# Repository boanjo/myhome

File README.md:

# myhome
A collection of mysensors nodes, gateways and HW from my home

I use a mix of NRF (2.4GHz) and RFM69 (433MHz) depending on the usage of the sensor. For longer distances i use RFM69 but they are a bit more power hungry so they all fill a purpose

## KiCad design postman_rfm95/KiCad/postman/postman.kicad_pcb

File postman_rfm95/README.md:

# Weather Station DC powered
This is my weatherstation for long range communication (20-100m) based on the MySensors framework https://www.mysensors.org/

The weather station is connecting 3 different sensors with water protected connections and casing. I've used a Adafruit PermaProto 1/2 sized board which works well here since it's mainly soldering of connectors we need to do and a few resistors.

The focus for this model is to protect the GX12 connections and the PCB but this with easy access. The box has plenty of room for the homemade 433MHz antenna:  http://www.byvac.com/downloads/RLnn/How-to-make-a-Air-Cooled-433MHz-antenna.pdf.

Fusion 360 - 3D printed parts
Download model from: https://www.thingiverse.com/thing:4652239

Youtube video: https://youtu.be/E27CFRdZH9k

Enjoy!

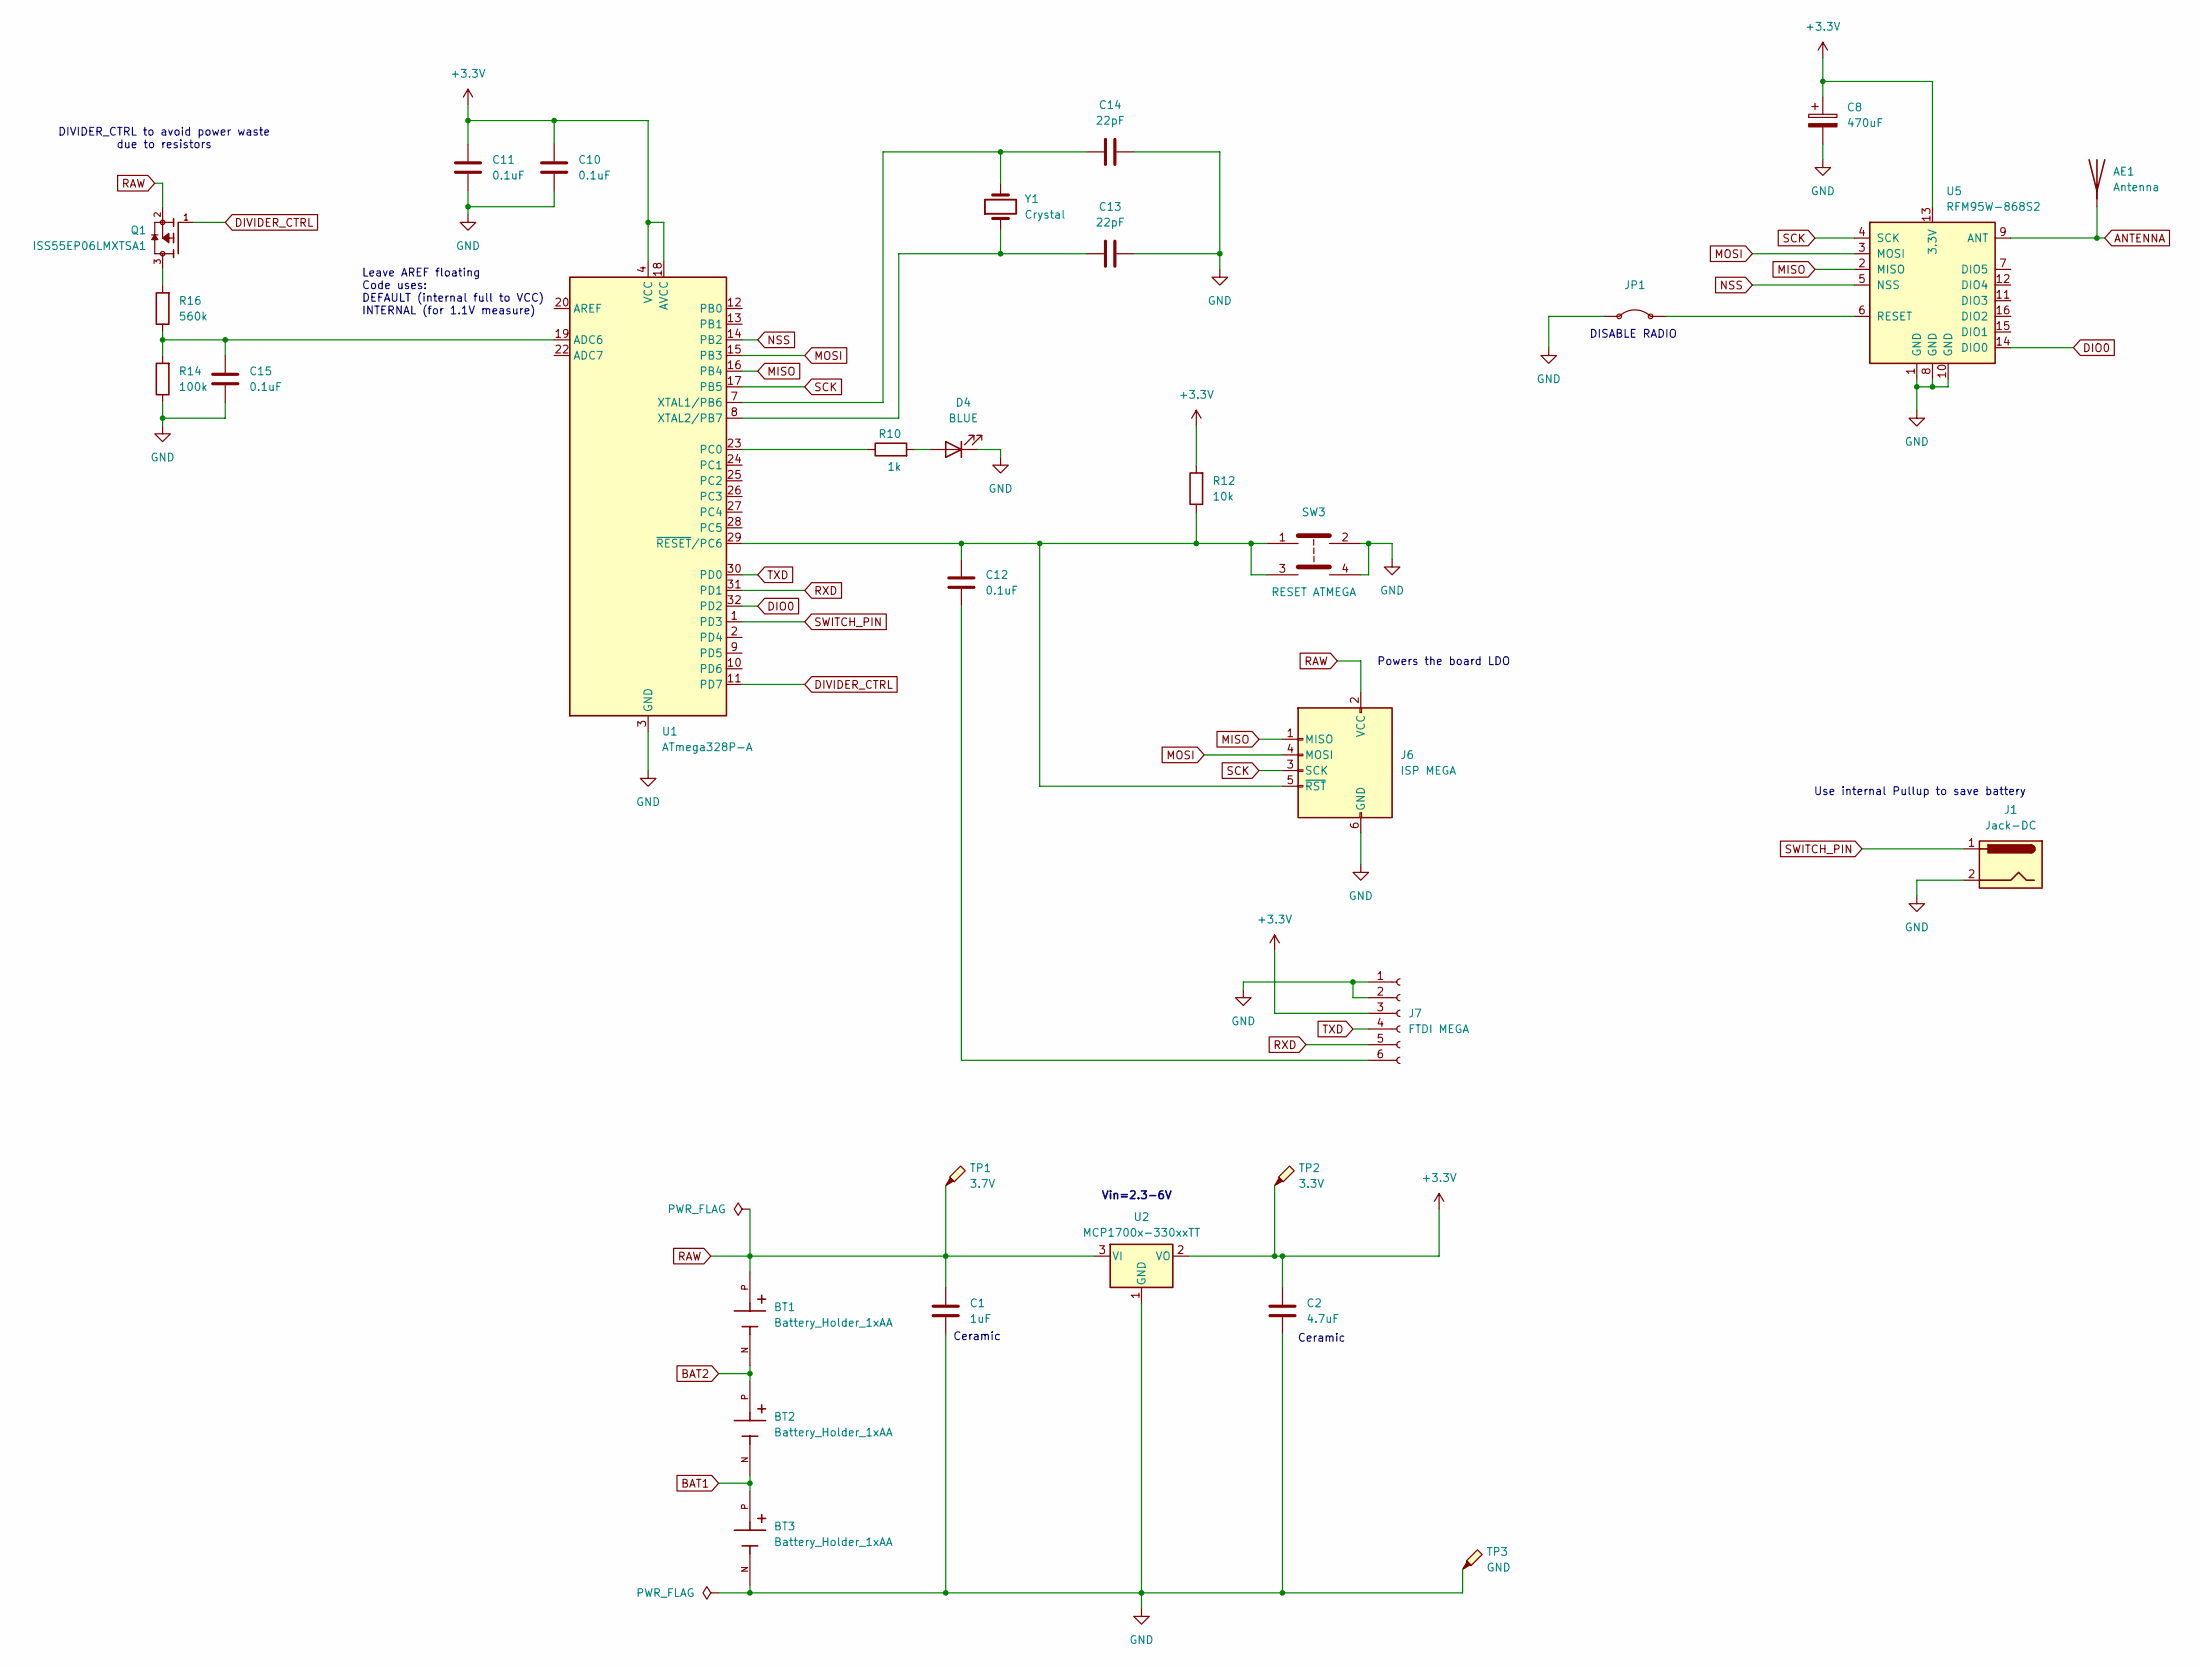
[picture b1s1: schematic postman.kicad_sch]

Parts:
AE1: Antenna; Antenna 868MHz
BT1, BT2, BT3: Battery_Holder_1xAA; Battery Holder 1xAA; PARTREV C
C1: 1uF; C_0805_2012Metric_Pad1.18x1.45mm_HandSolder
C2: 4.7uF; C_0805_2012Metric_Pad1.18x1.45mm_HandSolder
C8: 470uF; CP_Elec_10x10.5
C10, C11, C12, C15: 0.1uF; C_0805_2012Metric_Pad1.18x1.45mm_HandSolder
C13, C14: 22pF; C_0805_2012Metric_Pad1.18x1.45mm_HandSolder
D4: BLUE; LED_0805_2012Metric_Pad1.15x1.40mm_HandSolder
J1: Jack-DC; Jack DC
J6: ISP MEGA; AVR ISP 6p
J7: FTDI MEGA; FTDI 6p
JP1: Jumper 2p
Q1: ISS55EP06LMXTSA1; SOT-23_Handsoldering
R10: 1k; R_0805_2012Metric_Pad1.20x1.40mm_HandSolder
R12: 10k; R_0805_2012Metric_Pad1.20x1.40mm_HandSolder
R14: 100k; R_0805_2012Metric_Pad1.20x1.40mm_HandSolder
R16: 560k; R_0805_2012Metric_Pad1.20x1.40mm_HandSolder
SW3: RESET ATMEGA; tactile smd 13019319
TP1: 3.7V; Pin_D1.0mm_L10.0mm
TP2: 3.3V; Pin_D1.0mm_L10.0mm
TP3: GND; Pin_D1.0mm_L10.0mm
U1: ATmega328P-A; TQFP-32_7x7mm_P0.8mm
U2: MCP1700x-330xxTT; SOT-23_Handsoldering
U5: RFM95W-868S2; HOPERF_RFM9XW_SMD
Y1: Crystal; Crystal SMD FOXSDLF08020

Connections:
+3.3V: C2.1, C8.1, C10.1, C11.1, J7.3, R12.2, TP2.1, U1.4 (VCC), U1.6 (VCC), U1.18 (AVCC), U2.2 (VO), U5.13 (3.3V)
ANTENNA: AE1.1 (A), U5.9 (ANT)
BAT1: BT2.N, BT3.P
BAT2: BT1.N, BT2.P
DIO0: U1.32 (PD2), U5.14 (DIO0)
DIVIDER_CTRL: Q1.1, U1.11 (PD7)
GND: BT3.N, C1.2, C2.2, C8.2, C10.2, C11.2, C13.2, C14.2, C15.2, D4.1 (K), J1.2, J6.6 (GND), J7.1, J7.2, JP1.1, R14.1, SW3.2, SW3.4, TP3.1, U1.3 (GND), U1.5 (GND), U1.21 (GND), U2.1 (GND), U5.1 (GND), U5.8 (GND), U5.10 (GND)
MISO: J6.1 (MISO), U1.16 (PB4), U5.2 (MISO)
MOSI: J6.4 (MOSI), U1.15 (PB3), U5.3 (MOSI)
NSS: U1.14 (PB2), U5.5 (NSS)
unnamed: D4.2 (A), R10.2
unnamed: C12.1, J6.5 (~RST), R12.1, SW3.1, SW3.3, U1.29 (~RESET/PC6)
unnamed: C12.2, J7.6
unnamed: Q1.3, R16.2
unnamed: C15.1, R14.2, R16.1, U1.19 (ADC6)
unnamed: R10.1, U1.23 (PC0)
unnamed: C14.1, U1.7 (XTAL1/PB6), Y1.2
unnamed: C13.1, U1.8 (XTAL2/PB7), Y1.1
unnamed: JP1.2, U5.6 (RESET)
RAW: BT1.P, C1.1, J6.2 (VCC), Q1.2, TP1.1, U2.3 (VI)
RXD: J7.5, U1.31 (PD1)
SCK: J6.3 (SCK), U1.17 (PB5), U5.4 (SCK)
SWITCH_PIN: J1.1, U1.1 (PD3)
TXD: J7.4, U1.30 (PD0)

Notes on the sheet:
DIVIDER_CTRL to avoid power waste due to resistors
Ceramic
Use internal Pullup to save battery
Leave AREF floating Code uses: DEFAULT (internal full to VCC) INTERNAL (for 1.1V measure)
Vin=2.3-6V
DISABLE RADIO
Powers the board LDO

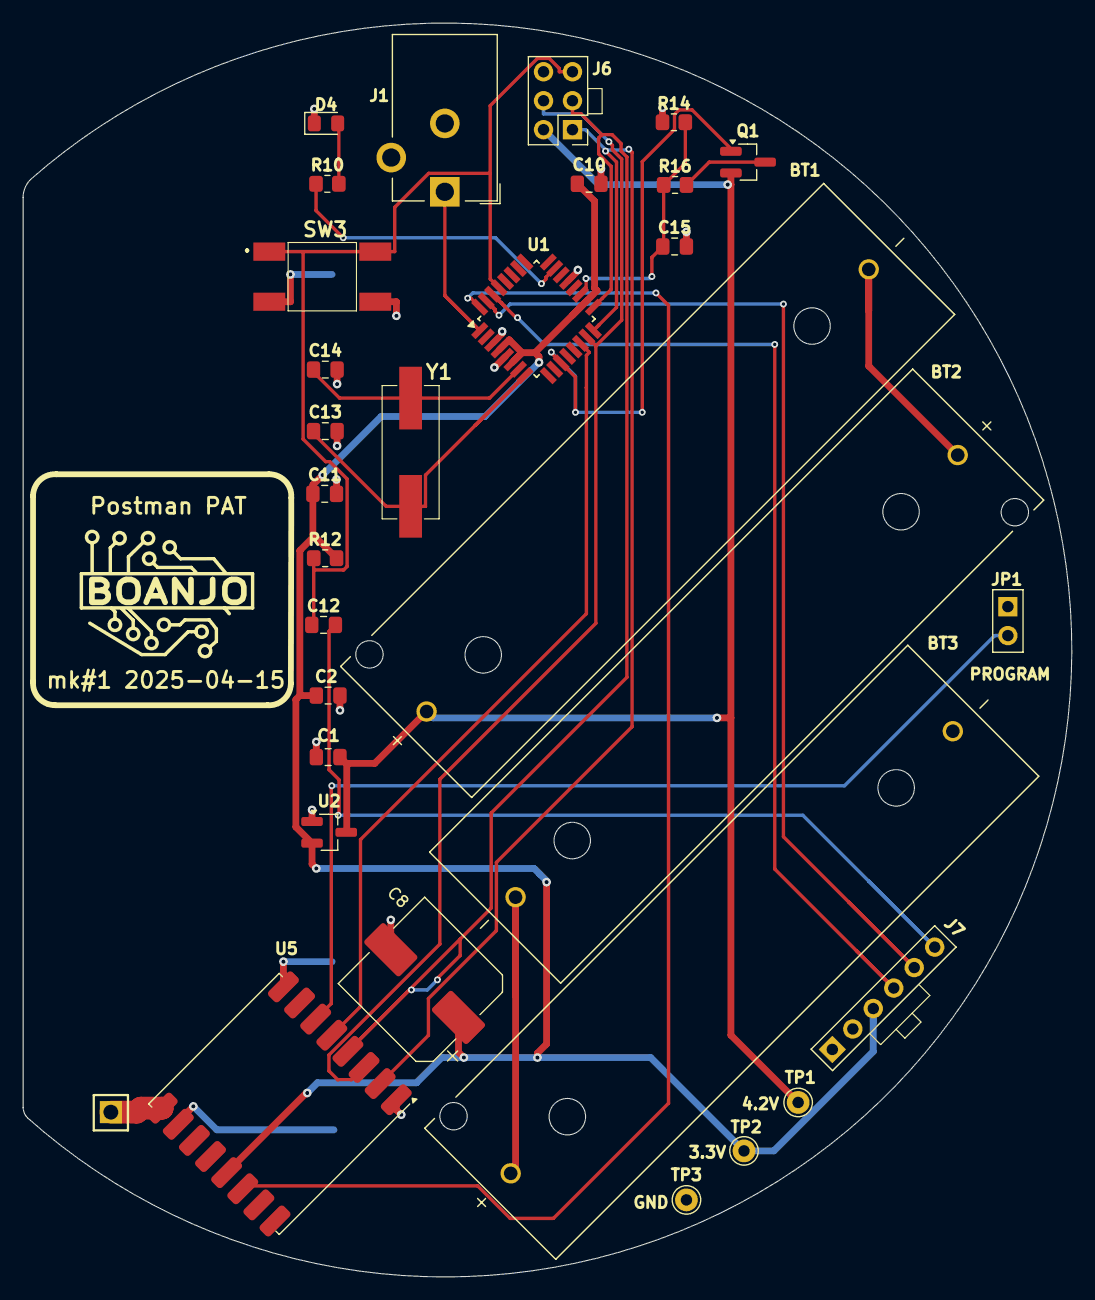
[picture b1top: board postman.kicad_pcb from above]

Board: 2 copper layers, 92.0 x 110.0 mm, 31 parts (0 on the bottom side), 24 nets.

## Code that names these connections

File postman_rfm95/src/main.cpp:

#include <Arduino.h>
#include <avr/sleep.h>

// #define MY_DEBUG  // Uncomment for development/debug

#define MY_RADIO_RFM95
#define MY_RFM95_FIXED_FREQUENCY_868MHZ
#define MY_RFM95_ATC_TARGET_RSSI_DBM (-70) // target RSSI -70dBm
#define MY_RFM95_MAX_POWER_LEVEL_DBM (20)  // max. TX power 10dBm = 10mW  20dBm = 100mW

#define MY_RFM95_NETWORKID (100)
#define MY_NODE_ID 70

#include <MySensors.h>

#define SWITCH_PIN 3           // PD3, digital pin 3, INT1
#define STATUS_PIN A0          // PC0, digital out or analog in
#define BATTERY_VOLTAGE_PIN A6 // ADC6, analog in only
#define DIVIDER_CTRL 7         // PD7, digital pin 7

#define CHILD_ID_POST 1
#define CHILD_ID_SEND_RSSI 2
#define CHILD_ID_REC_RSSI 3
#define CHILD_ID_TX_POWER 4
#define CHILD_ID_BATTERY 5
#define CHILD_ID_TRIP_CNT 6

MyMessage msgPost(CHILD_ID_POST, V_TRIPPED);
MyMessage msgSendRssi(CHILD_ID_SEND_RSSI, V_LEVEL);
MyMessage msgRecRssi(CHILD_ID_REC_RSSI, V_LEVEL);
MyMessage msgTxPower(CHILD_ID_TX_POWER, V_LEVEL);
MyMessage msgBatteryVoltage(CHILD_ID_BATTERY, V_VOLTAGE);
MyMessage msgTripCnt(CHILD_ID_TRIP_CNT, V_KWH);

bool tripped = false;

#define SLEEP_TIME (12L * 60L * 60L * 1000L)  // Twice a day
uint32_t sleepTime = SLEEP_TIME;
int8_t wakeupReason = MY_WAKE_UP_BY_TIMER;

void setup() {
#ifdef MY_DEBUG
  Serial.begin(115200);
  while (!Serial);
  Serial.println("Starting Postman Pat");
#endif

  pinMode(STATUS_PIN, OUTPUT);
  digitalWrite(STATUS_PIN, LOW);

  pinMode(SWITCH_PIN, INPUT_PULLUP);
  pinMode(DIVIDER_CTRL, OUTPUT);
  digitalWrite(DIVIDER_CTRL, LOW);

  analogReference(INTERNAL);  // 1.1V for AREF
}

void presentation() {
  sendSketchInfo("Postman Pat", "0.2");

  present(CHILD_ID_POST, S_MOTION);
  present(CHILD_ID_SEND_RSSI, S_SOUND);
  present(CHILD_ID_REC_RSSI, S_SOUND);
  present(CHILD_ID_TX_POWER, S_SOUND);
  present(CHILD_ID_BATTERY, S_MULTIMETER);
  present(CHILD_ID_BATTERY, S_MULTIMETER);
  present(CHILD_ID_TRIP_CNT, S_POWER);}


uint16_t tripCount = 0;

void loop() {
  wakeupReason = sleep(digitalPinToInterrupt(SWITCH_PIN), CHANGE, sleepTime);

#ifdef MY_DEBUG
  Serial.println("Woke up");
#endif

  digitalWrite(STATUS_PIN, HIGH);
  digitalWrite(DIVIDER_CTRL, HIGH);
  delay(10);  // optional stabilization

  int raw = analogRead(BATTERY_VOLTAGE_PIN);
  digitalWrite(DIVIDER_CTRL, LOW);
  float batteryVoltage = raw * 0.006628855;
  send(msgBatteryVoltage.set(batteryVoltage, 2));

  int16_t txRssi = RFM95_getSendingRSSI();
  int16_t rxRssi = RFM95_getReceivingRSSI();
  uint8_t txPower = RFM95_getTxPowerLevel();

#ifdef MY_DEBUG
  Serial.print("Battery: "); Serial.println(batteryVoltage);
  Serial.print("TX RSSI: "); Serial.println(txRssi);
  Serial.print("RX RSSI: "); Serial.println(rxRssi);
  Serial.print("TX Power: "); Serial.println(txPower);
  Serial.print("Trip cnt: "); Serial.println(tripCount);
#endif

  if (wakeupReason == digitalPinToInterrupt(SWITCH_PIN)) {
    sleepTime = getSleepRemaining();
    tripped = !tripped;
    send(msgPost.set(tripped ? "1" : "0"));
    tripCount++;
  } else {
    sleepTime = SLEEP_TIME;
  }  

  send(msgSendRssi.set(txRssi));
  send(msgRecRssi.set(rxRssi));
  send(msgTxPower.set(txPower));
  send(msgTripCnt.set(tripCount));


  digitalWrite(DIVIDER_CTRL, LOW); // disable voltage divider
  digitalWrite(STATUS_PIN, LOW);
  delay(100);
}

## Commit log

2018-12-28 Added Christmas sensor
2019-01-12 Added garage door opener
2019-01-13 added serial GW
2019-03-08 Added Text sensor for status
2019-03-08 rename sketch
2019-03-08 renamed sketchs
2019-03-08 Added 2.4GHz sensors
2019-07-12 Added presence check for Robot Mower
2020-10-17 Added a batch of sensors
2020-10-27 Added anemometer and rain_gauge sensors
2020-10-27 Added sensor ids
2020-10-27 Added temp indoor with RSSI + battery report
2020-10-27 change of repo name for image
2020-10-27 Changed repo name for images
2020-10-28 Added YouTube link for attiny exampe
2020-10-28 Added README
2020-10-30 updated YouTube link
2020-10-30 Added README for rain sensor
2020-10-31 Updated thingiverse link
2020-11-02 added
2020-11-02 added calibration
2020-11-02 Added youtube for rain_gauge
2020-11-03 mqtt gw
2020-11-12 added weatherstation
2020-11-13 updates for ws
2020-11-16 added mqtt gw for platformio
2020-11-16 adding gitignore
2020-11-18 Added README for gataway_mqtt
2020-11-18 added thing
2020-12-11 Added dv powered temp indoor
2020-12-22 sensor updates
2025-03-09 Added KiCad drawings for WS3.0
2025-03-31 Updates for mk #5
2025-04-01 first ws3.0 draft
2025-04-16 PCBWAYs delivery 2025-04-16 mk#5 of ws3.0
2025-04-16 Updates to postman and temperature after PCB layout
